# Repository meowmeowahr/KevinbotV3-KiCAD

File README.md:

# This repository has moved

Kevinbot Core and the Kevinbot P2 Board have split into separate repositories, and are now located in the [Kevinbot Robotics](https://github.com/Kevinbot-Robotics) organization.

## Kevinbot Core (aka RevB)

https://github.com/Kevinbot-Robotics/kevinbot_core

## Kevinbot P2 Board (aka RevA)

https://github.com/Kevinbot-Robotics/kevinbot_p2_board

## PCBWay

</img>

Thanks to PCBWay for providing high-quality PCB prototypes.

I would recommend them for any of your PCB needs. They offer fast turnaround and shipping.

[Get a Quote Here](https://www.pcbway.com/orderonline.aspx)

</img>
</img>

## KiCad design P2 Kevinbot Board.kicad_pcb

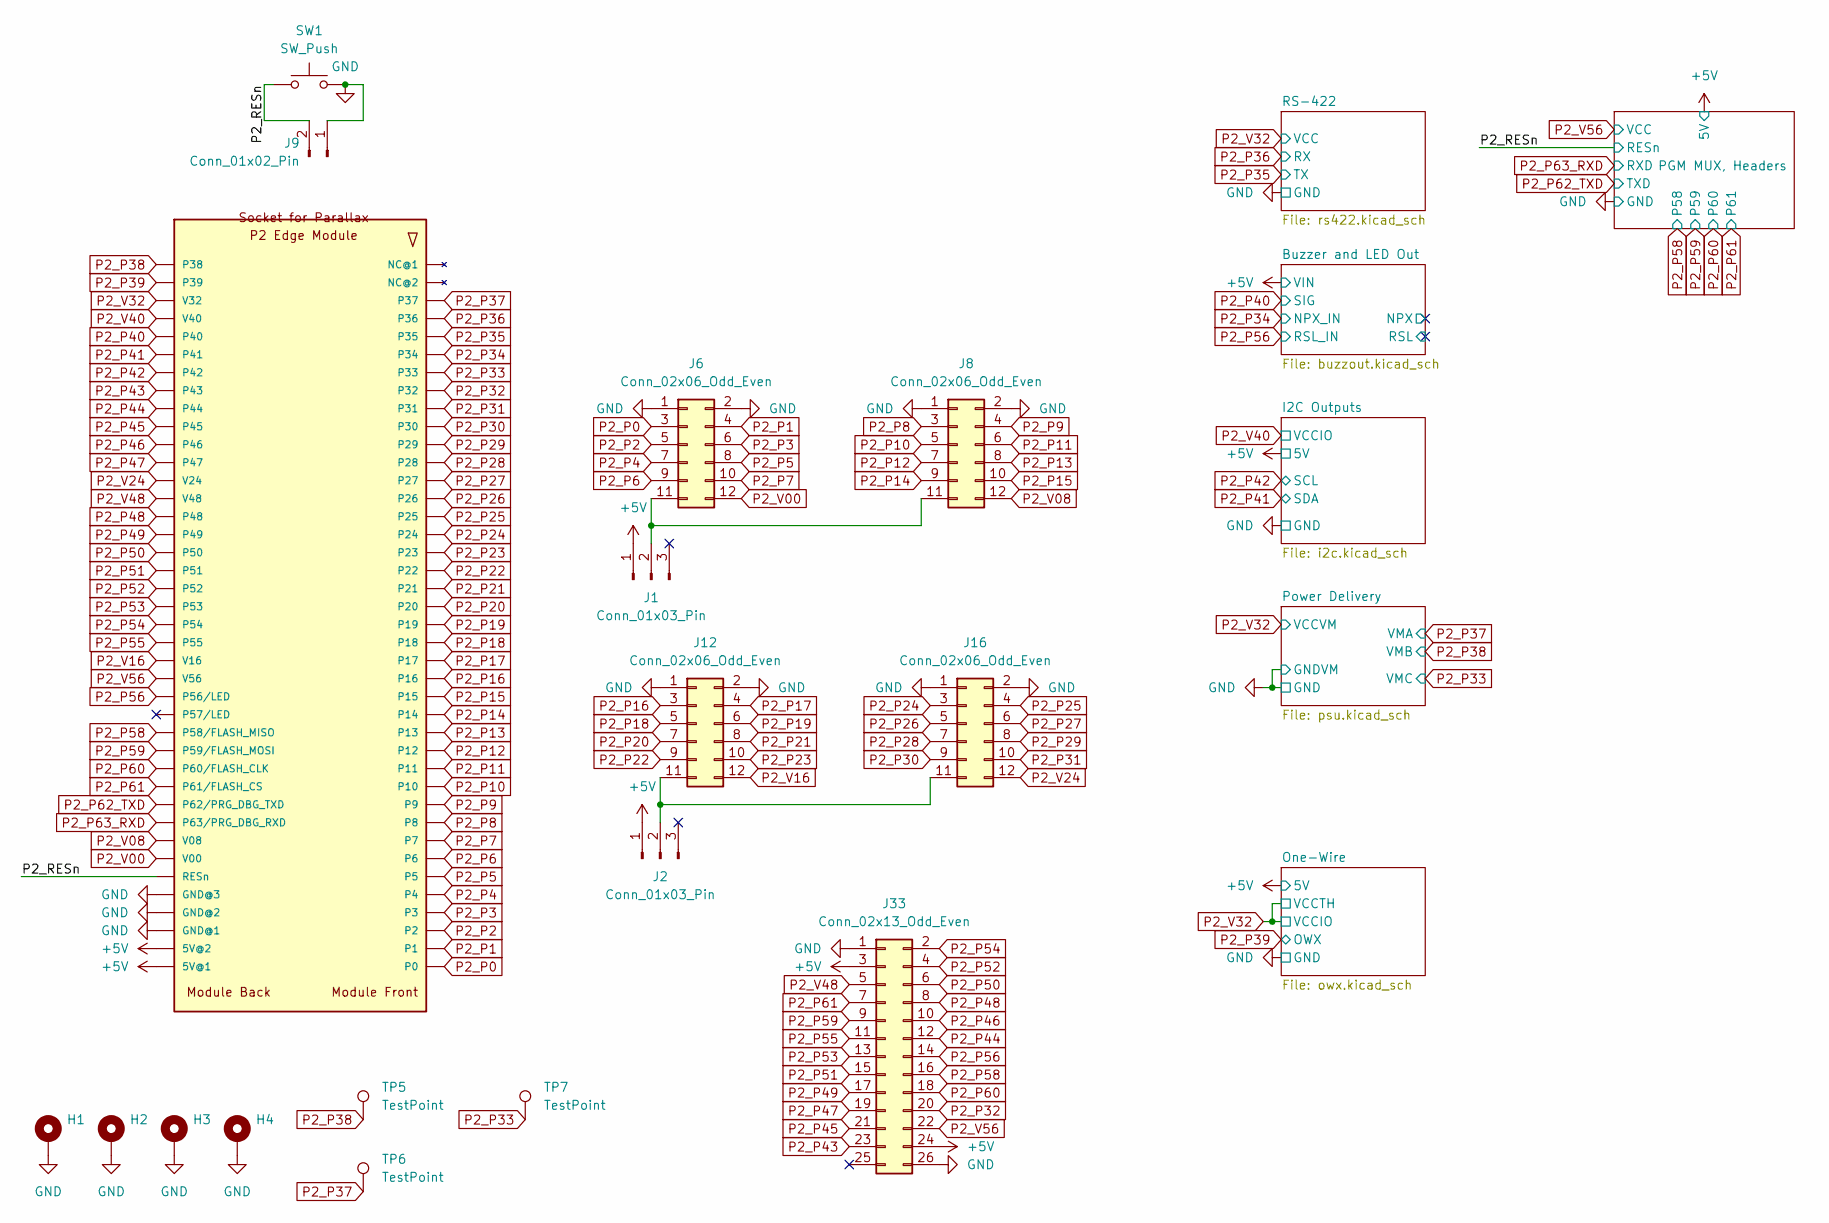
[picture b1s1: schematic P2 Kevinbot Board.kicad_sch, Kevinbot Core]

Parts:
H1, H2, H3, H4: MountingHole_Pad; MountingHole_3.2mm_M3_Pad
J1, J2: Conn_01x03_Pin; PinHeader_1x03_P2.00mm_Vertical; Part Number 2PH1-03-UA, SPN02SXCN-RC
J6, J8, J12, J16: Conn_02x06_Odd_Even; PinHeader_2x06_P2.54mm_Vertical; Part Number G800W590018EU
J9: Conn_01x02_Pin; Molex_Nano-Fit_105309-xx02_1x02_P2.50mm_Vertical; Part Number 1053091102
J33: Conn_02x13_Odd_Even; PinHeader_2x13_P1.27mm_Vertical; Part Number 3220-26-0100-00
SW1: SW_Push; SW_SPST_PTS645Sx43SMTR92; Part Number PTS645SM43SMTR92 LFS
TP5, TP6, TP7: TestPoint; TestPoint_Pad_D1.0mm
U1: P2_EDGE_MODULE_SOCKET; Card_Edge_TH_RA_1.27mm_80p; Part Number 450-00308

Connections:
+5V: J1.1, J2.1, J33.3, J33.24, U1.41 (5V@1), U1.42 (5V@2); also elsewhere on the board
/P2_RESn: J9.2, SW1.1, U1.46 (RESn); also elsewhere on the board
GND: H1.1, H2.1, H3.1, H4.1, J6.1, J6.2, J8.1, J8.2, J9.1, J12.1, J12.2, J16.1, J16.2, J33.1, J33.26, SW1.2, U1.43 (GND@1), U1.44 (GND@2), U1.45 (GND@3); also elsewhere on the board
unnamed: J1.2, J6.11, J8.11
unnamed: J2.2, J12.11, J16.11
P2_P0: J6.3, U1.40 (P0)
P2_P1: J6.4, U1.39 (P1)
P2_P2: J6.5, U1.38 (P2)
P2_P3: J6.6, U1.37 (P3)
P2_P4: J6.7, U1.36 (P4)
P2_P5: J6.8, U1.35 (P5)
P2_P6: J6.9, U1.34 (P6)
P2_P7: J6.10, U1.33 (P7)
P2_P8: J8.3, U1.32 (P8)
P2_P9: J8.4, U1.31 (P9)
P2_P10: J8.5, U1.30 (P10)
P2_P11: J8.6, U1.29 (P11)
P2_P12: J8.7, U1.28 (P12)
P2_P13: J8.8, U1.27 (P13)
P2_P14: J8.9, U1.26 (P14)
P2_P15: J8.10, U1.25 (P15)
P2_P16: J12.3, U1.24 (P16)
P2_P17: J12.4, U1.23 (P17)
P2_P18: J12.5, U1.22 (P18)
P2_P19: J12.6, U1.21 (P19)
P2_P20: J12.7, U1.20
P2_P21: J12.8, U1.19 (P21)
P2_P22: J12.9, U1.18 (P22)
P2_P23: J12.10, U1.17 (P23)
P2_P24: J16.3, U1.16 (P24)
P2_P25: J16.4, U1.15 (P25)
P2_P26: J16.5, U1.14 (P26)
P2_P27: J16.6, U1.13 (P27)
P2_P28: J16.7, U1.12 (P28)
P2_P29: J16.8, U1.11 (P29)
P2_P30: J16.9, U1.10 (P30)
P2_P31: J16.10, U1.9 (P31)
P2_P32: J33.20, U1.8 (P32)
P2_P33: TP7.1, U1.7 (P33); also elsewhere on the board
P2_P34: U1.6 (P34); also elsewhere on the board
P2_P35: U1.5 (P35); also elsewhere on the board
P2_P36: U1.4 (P36); also elsewhere on the board
P2_P37: TP6.1, U1.3 (P37); also elsewhere on the board
P2_P38: TP5.1, U1.80 (P38); also elsewhere on the board
P2_P39: U1.79 (P39); also elsewhere on the board
P2_P40: U1.76 (P40); also elsewhere on the board
P2_P41: U1.75 (P41); also elsewhere on the board
P2_P42: U1.74 (P42); also elsewhere on the board
P2_P43: J33.23, U1.73 (P43)
P2_P44: J33.12, U1.72 (P44)
P2_P45: J33.21, U1.71 (P45)
P2_P46: J33.10, U1.70 (P46)
P2_P47: J33.19, U1.69 (P47)
P2_P48: J33.8, U1.66 (P48)
P2_P49: J33.17, U1.65 (P49)
P2_P50: J33.6, U1.64 (P50)
P2_P51: J33.15, U1.63 (P51)
P2_P52: J33.4, U1.62 (P52)
P2_P53: J33.13, U1.61 (P53)
P2_P54: J33.2, U1.60 (P54)
P2_P55: J33.11, U1.59 (P55)
P2_P56: J33.14, U1.56 (P56/LED); also elsewhere on the board
P2_P58: J33.16, U1.54 (P58/FLASH_MISO); also elsewhere on the board
P2_P59: J33.9, U1.53 (P59/FLASH_MOSI); also elsewhere on the board
P2_P60: J33.18, U1.52 (P60/FLASH_CLK); also elsewhere on the board
P2_P61: J33.7, U1.51 (P61/FLASH_CS); also elsewhere on the board
P2_P62_TXD: U1.50 (P62/PRG_DBG_TXD); also elsewhere on the board
P2_P63_RXD: U1.49 (P63/PRG_DBG_RXD); also elsewhere on the board
P2_V00: J6.12, U1.47 (V00)
P2_V08: J8.12, U1.48 (V08)
P2_V16: J12.12, U1.58 (V16)
P2_V24: J16.12, U1.68 (V24)
P2_V32: U1.78 (V32); also elsewhere on the board
P2_V40: U1.77 (V40); also elsewhere on the board
P2_V48: J33.5, U1.67 (V48)
P2_V56: J33.22, U1.57 (V56); also elsewhere on the board

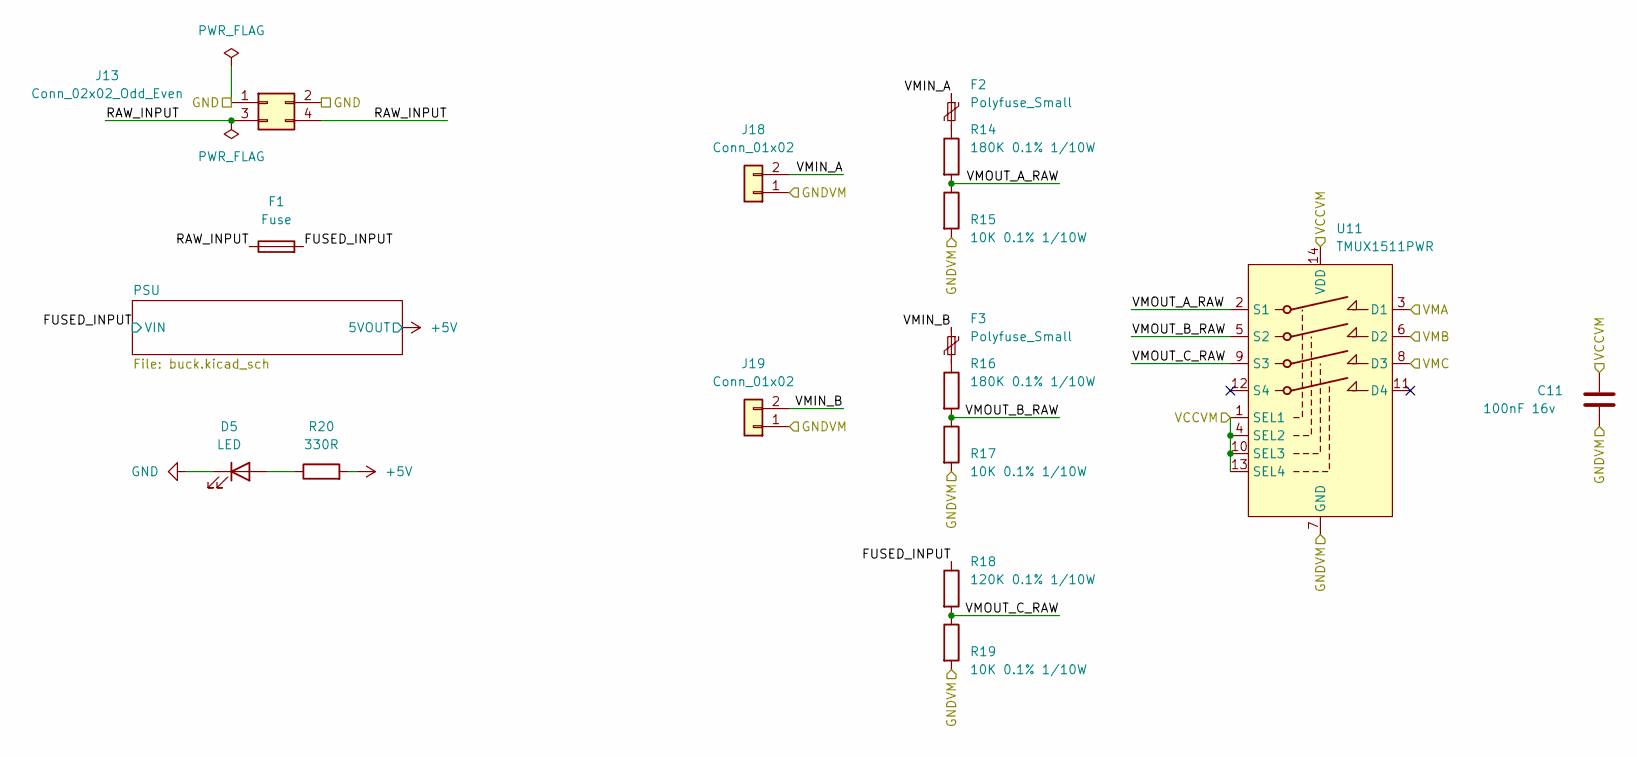
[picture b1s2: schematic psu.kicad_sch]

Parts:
C11: 100nF 16v; C_0402_1005Metric; Part Number GRM155R71C104KA88D
D5: LED; LED_0603_1608Metric; Part Number 150080SS75000
F1: Fuse; Fuseholder_Blade_Mini_Keystone_3568; Part Number 3568
F2, F3: Polyfuse_Small; Fuse_1206_3216Metric_Pad1.42x1.75mm_HandSolder; Part Number 0ZCJ0005FF2E
J13: Conn_02x02_Odd_Even; Molex_Micro-Fit_3.0_43045-0400_2x02_P3.00mm_Horizontal; Part Number 0430450400
J18, J19: Conn_01x02; Molex_Nano-Fit_105313-xx02_1x02_P2.50mm_Horizontal; Part Number 1053132102
R14, R16: 180K 0.1% 1/10W; R_0603_1608Metric; Part Number RT0603BRD07180KL
R15, R17, R19: 10K 0.1% 1/10W; R_0603_1608Metric; Part Number RT0603BRD0710KL
R18: 120K 0.1% 1/10W; R_0603_1608Metric; Part Number RT0603BRD07120KL
R20: 330R; R_0603_1608Metric; Part Number RC0402FR-07330RL
U11: TMUX1511PWR; TSSOP-14_4.4x5mm_P0.65mm; Part Number TMUX1511PWR

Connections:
+5V: R20.2; also elsewhere on the board
/Power Delivery/FUSED_INPUT: F1.2, R18.1; also elsewhere on the board
/Power Delivery/RAW_INPUT: F1.1, J13.3, J13.4
/Power Delivery/VMIN_A: F2.1, J18.2
/Power Delivery/VMIN_B: F3.1, J19.2
/Power Delivery/VMOUT_A_RAW: R14.2, R15.1, U11.2 (S1)
/Power Delivery/VMOUT_B_RAW: R16.2, R17.1, U11.5 (S2)
/Power Delivery/VMOUT_C_RAW: R18.2, R19.1, U11.9 (S3)
GND: C11.1, D5.1 (K), J13.1, J13.2, J18.1, J19.1, R15.2, R17.2, R19.2, U11.7 (GND); also elsewhere on the board
unnamed: D5.2 (A), R20.1
unnamed: F2.2, R14.1
unnamed: F3.2, R16.1
P2_P33: U11.8 (D3); also elsewhere on the board
P2_P37: U11.3 (D1); also elsewhere on the board
P2_P38: U11.6 (D2); also elsewhere on the board
P2_V32: C11.2, U11.1 (SEL1), U11.4 (SEL2), U11.10 (SEL3), U11.13 (SEL4), U11.14 (VDD); also elsewhere on the board

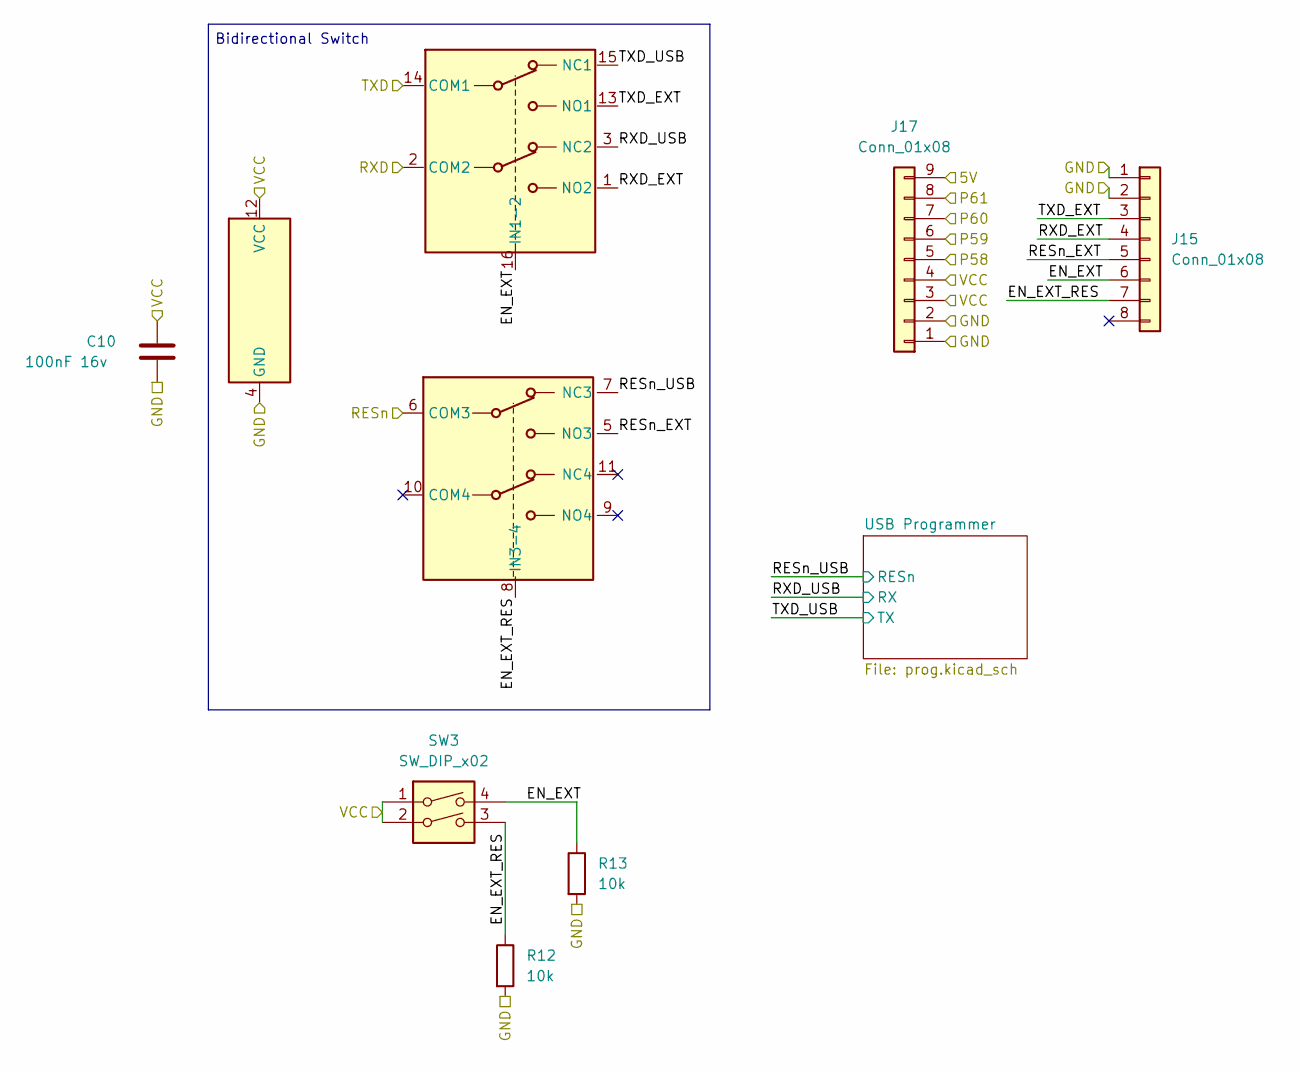
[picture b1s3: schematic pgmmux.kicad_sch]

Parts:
C10: 100nF 16v; C_0402_1005Metric; Part Number GRM155R71C104KA88D
J15: Conn_01x08; PinSocket_1x08_P2.54mm_Vertical; Part Number PPTC081LFBN-RC
J17: Conn_01x08; PinSocket_1x09_P2.54mm_Vertical; Part Number PPTC091LFBN-RC
R12, R13: 10k; R_0402_1005Metric; Part Number RC0402FR-0710KL
SW3: SW_DIP_x02; SW_DIP_SPSTx02_Slide_Copal_CHS-02A_W5.08mm_P1.27mm_JPin; Part Number CHS-02TA
U10: TS3A44159PWR; TSSOP-16_4.4x5mm_P0.65mm; Part Number TS3A44159PWR

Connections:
+5V: J17.9; also elsewhere on the board
/P2_RESn: U10.6 (COM3); also elsewhere on the board
/PGM MUX, Headers/EN_EXT: J15.6, R13.1, SW3.4, U10.16 (IN1-2)
/PGM MUX, Headers/EN_EXT_RES: J15.7, R12.1, SW3.3, U10.8 (IN3-4)
/PGM MUX, Headers/RESn_EXT: J15.5, U10.5 (NO3)
/PGM MUX, Headers/RESn_USB: U10.7 (NC3); also elsewhere on the board
/PGM MUX, Headers/RXD_EXT: J15.4, U10.1 (NO2)
/PGM MUX, Headers/RXD_USB: U10.3 (NC2); also elsewhere on the board
/PGM MUX, Headers/TXD_EXT: J15.3, U10.13 (NO1)
/PGM MUX, Headers/TXD_USB: U10.15 (NC1); also elsewhere on the board
GND: C10.1, J15.1, J15.2, J17.1, J17.2, R12.2, R13.2, U10.4 (GND); also elsewhere on the board
P2_P58: J17.5; also elsewhere on the board
P2_P59: J17.6; also elsewhere on the board
P2_P60: J17.7; also elsewhere on the board
P2_P61: J17.8; also elsewhere on the board
P2_P62_TXD: U10.14 (COM1); also elsewhere on the board
P2_P63_RXD: U10.2 (COM2); also elsewhere on the board
P2_V56: C10.2, J17.3, J17.4, SW3.1, SW3.2, U10.12 (VCC); also elsewhere on the board

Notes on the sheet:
Bidirectional Switch

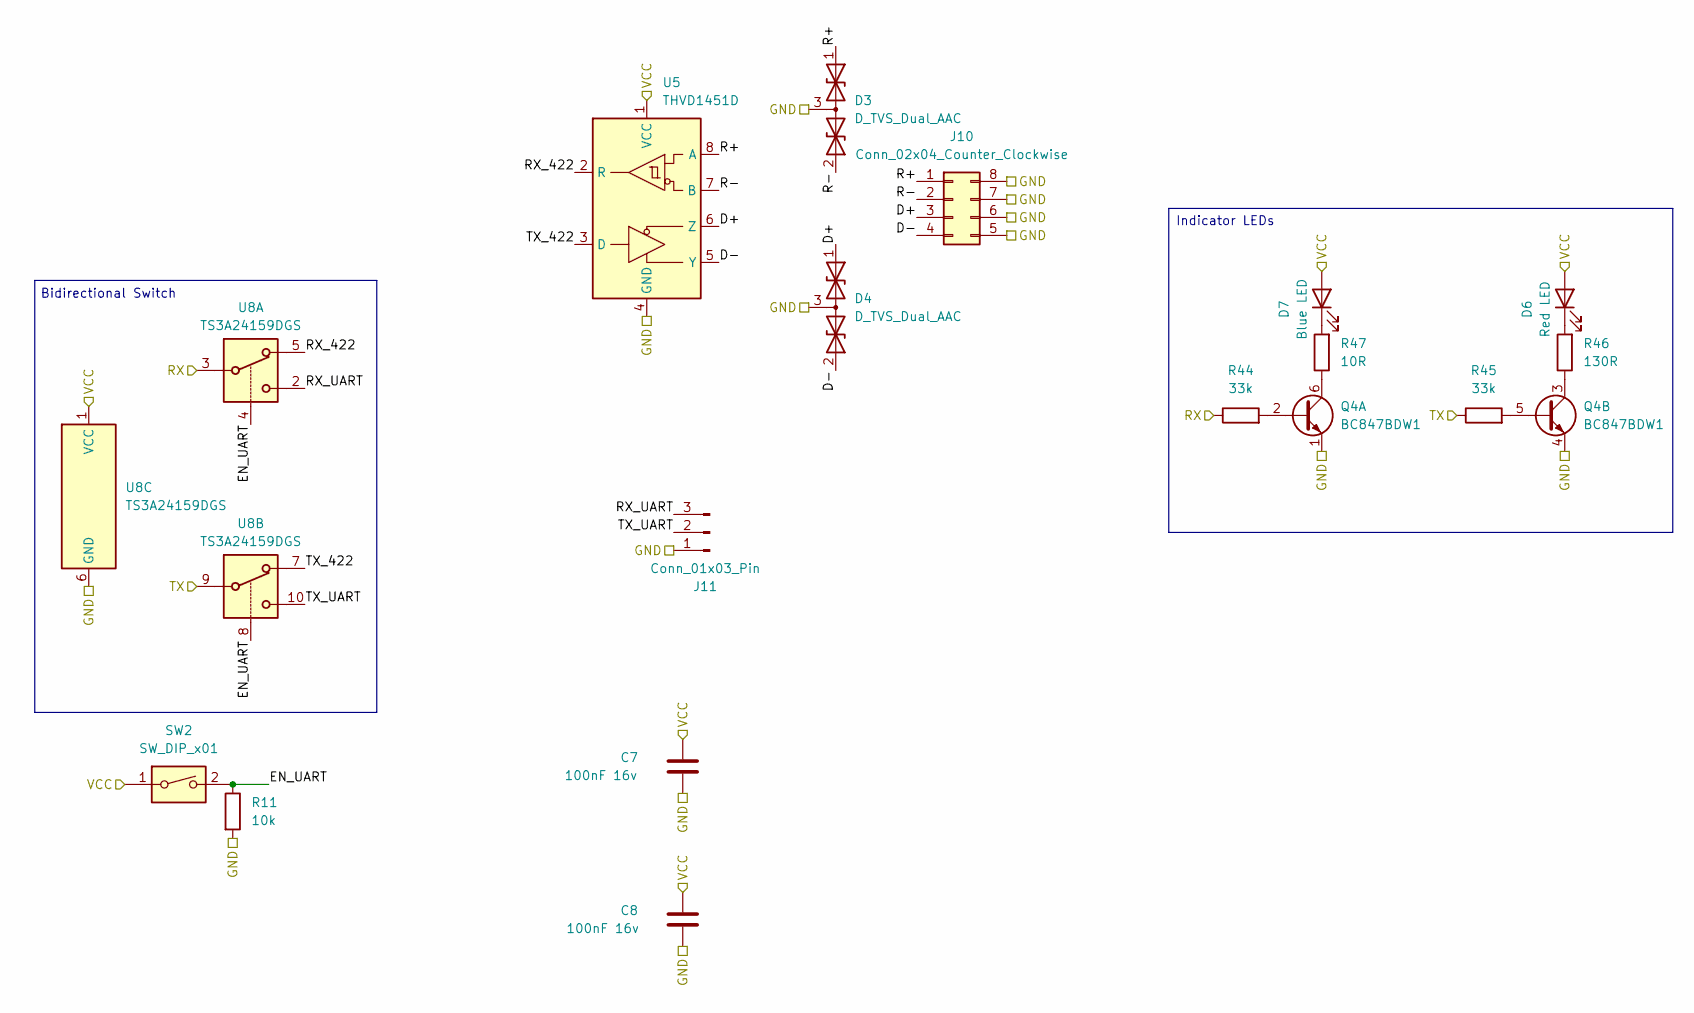
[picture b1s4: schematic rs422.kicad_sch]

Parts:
C7, C8: 100nF 16v; C_0402_1005Metric; Part Number GRM155R71C104KA88D
D3, D4: D_TVS_Dual_AAC; SOT-23; Part Number D5V0L2B3SO-7
D6: Red LED; LED_0603_1608Metric; Part Number 150060RS75000
D7: Blue LED; LED_0603_1608Metric; Part Number 150060BS75000
J10: Conn_02x04_Counter_Clockwise; Molex_Nano-Fit_105310-xx08_2x04_P2.50mm_Vertical; Part Number 1053101108
J11: Conn_01x03_Pin; JST_PH_B3B-PH-K_1x03_P2.00mm_Vertical; Part Number B3B-PH-K-S
Q4: BC847BDW1; SOT-363_SC-70-6; Part Number BC847BDW1T1G
R11: 10k; R_0402_1005Metric; Part Number RC0402FR-0710KL
R44, R45: 33k; R_0402_1005Metric; Part Number RC0402FR-0733KL
R46: 130R; R_0402_1005Metric; Part Number RC0402FR-07130RL
R47: 10R; R_0402_1005Metric; Part Number RC0402FR-0710RL
SW2: SW_DIP_x01; SW_DIP_SPSTx01_Slide_Copal_CHS-01A_W5.08mm_P1.27mm_JPin; Part Number CHS-01A
U5: THVD1451D; SOIC-8_3.9x4.9mm_P1.27mm; Part Number THVD1451D
U8: TS3A24159DGS; TSSOP-10_3x3mm_P0.5mm; Part Number TS3A24159DGSR

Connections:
/RS-422/D+: D4.1 (A1), J10.3, U5.6 (Z)
/RS-422/D-: D4.2 (A2), J10.4, U5.5 (Y)
/RS-422/EN_UART: R11.1, SW2.2, U8.4, U8.8
/RS-422/R+: D3.1 (A1), J10.1, U5.8 (A)
/RS-422/R-: D3.2 (A2), J10.2, U5.7 (B)
/RS-422/RX_422: U5.2 (R), U8.5
/RS-422/RX_UART: J11.3, U8.2
/RS-422/TX_422: U5.3 (D), U8.7
/RS-422/TX_UART: J11.2, U8.10
GND: C7.1, C8.1, D3.3 (common), D4.3 (common), J10.5, J10.6, J10.7, J10.8, J11.1, Q4.1 (E1), Q4.4 (E2), R11.2, U5.4 (GND), U8.6 (GND); also elsewhere on the board
unnamed: D6.1 (K), R46.2
unnamed: D7.1 (K), R47.2
unnamed: Q4.2 (B1), R44.2
unnamed: Q4.6 (C1), R47.1
unnamed: Q4.5 (B2), R45.2
unnamed: Q4.3 (C2), R46.1
P2_P35: R45.1, U8.9; also elsewhere on the board
P2_P36: R44.1, U8.3; also elsewhere on the board
P2_V32: C7.2, C8.2, D6.2 (A), D7.2 (A), SW2.1, U5.1 (VCC), U8.1 (VCC); also elsewhere on the board

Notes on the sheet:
Bidirectional Switch
Indicator LEDs

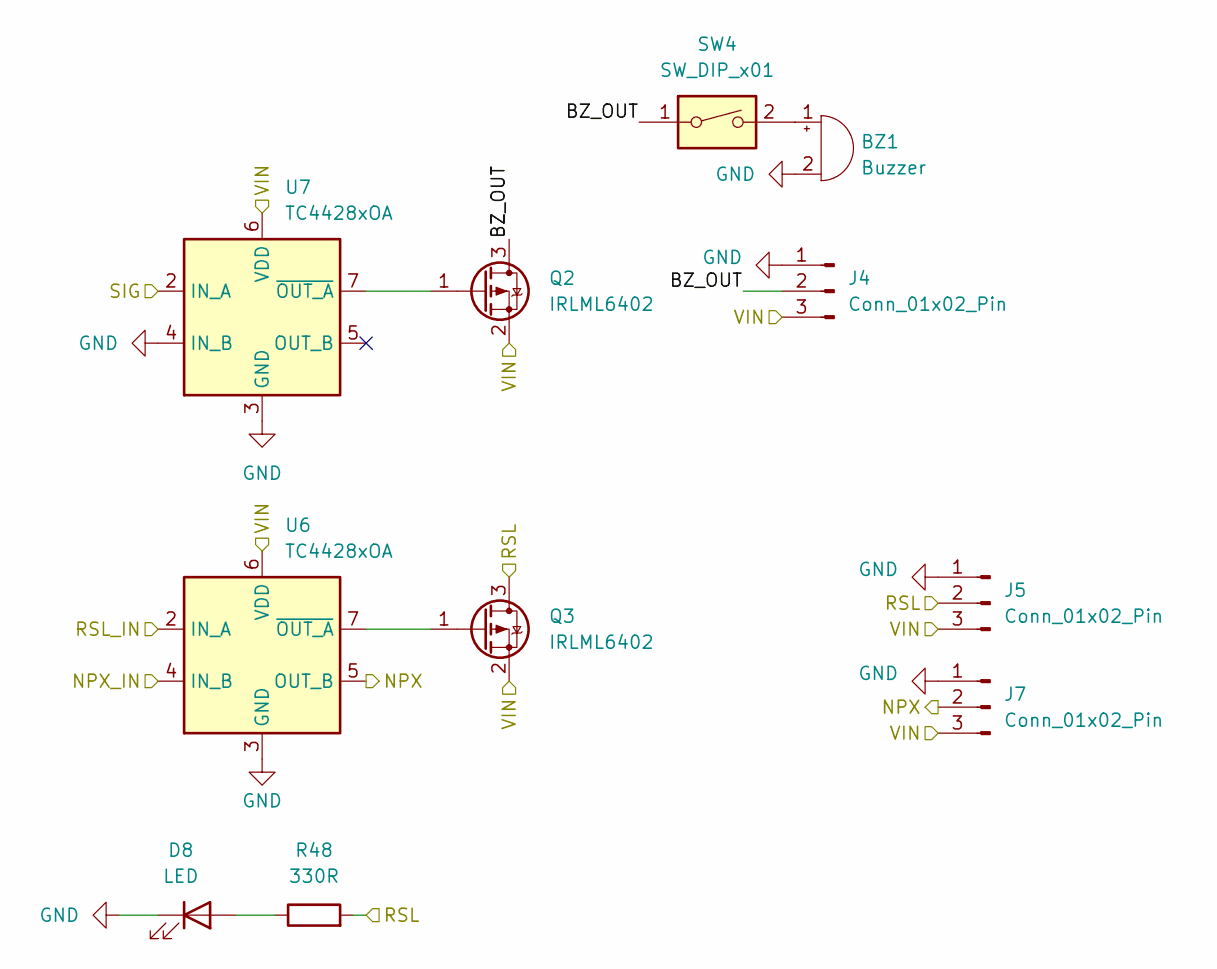
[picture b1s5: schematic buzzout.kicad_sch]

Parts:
BZ1: Buzzer; Buzzer_TDK_PS1240P02BT_D12.2mm_H6.5mm; Part Number PS1240P02BT
D8: LED; LED_0603_1608Metric; Part Number 150060YS75000
J4, J5, J7: Conn_01x02_Pin; Molex_Nano-Fit_105309-xx03_1x03_P2.50mm_Vertical; Part Number 1053091103
Q2, Q3: IRLML6402; SOT-23; Part Number IRLML6402TRPBF
R48: 330R; R_0603_1608Metric; Part Number RC0402FR-07330RL
SW4: SW_DIP_x01; SW_DIP_SPSTx01_Slide_Copal_CHS-01A_W5.08mm_P1.27mm_JPin; Part Number CHS-01A
U6, U7: TC4428xOA; SOIC-8_3.9x4.9mm_P1.27mm; Part Number TC4428EOA713

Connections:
+5V: J4.3, J5.3, J7.3, Q2.2 (S), Q3.2 (S), U6.6 (VDD), U7.6 (VDD); also elsewhere on the board
/Buzzer and LED Out/BZ_OUT: J4.2, Q2.3 (D), SW4.1
/Buzzer and LED Out/NPX: J7.2, U6.5 (OUT_B)
/Buzzer and LED Out/RSL: J5.2, Q3.3 (D), R48.2
GND: BZ1.2 (-), D8.1 (K), J4.1, J5.1, J7.1, U6.3 (GND), U7.3 (GND), U7.4 (IN_B); also elsewhere on the board
unnamed: BZ1.1 (+), SW4.2
unnamed: D8.2 (A), R48.1
unnamed: Q2.1 (G), U7.7 (~OUT_A)
unnamed: Q3.1 (G), U6.7 (~OUT_A)
P2_P34: U6.4 (IN_B); also elsewhere on the board
P2_P40: U7.2 (IN_A); also elsewhere on the board
P2_P56: U6.2 (IN_A); also elsewhere on the board

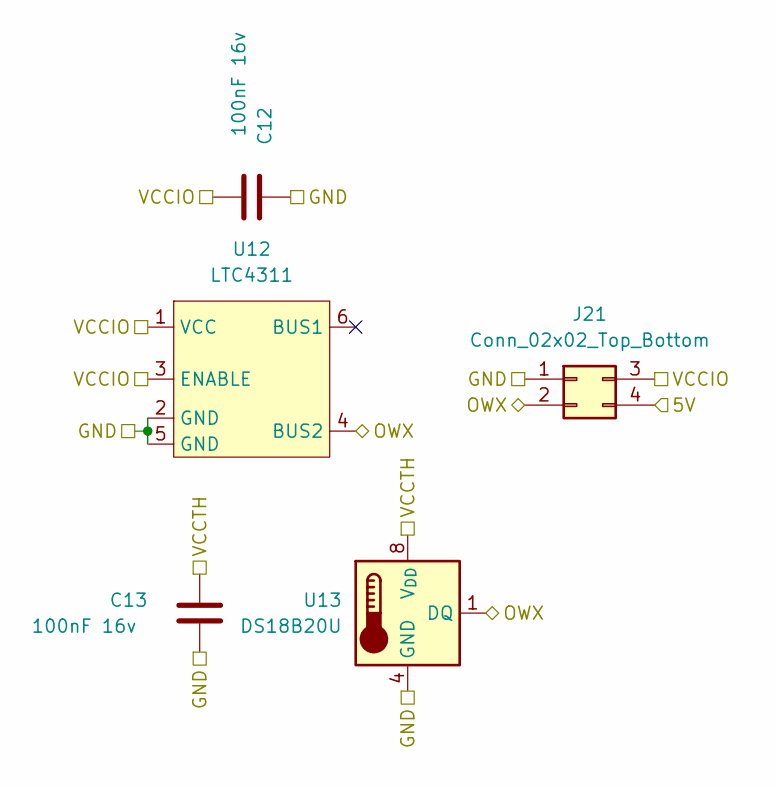
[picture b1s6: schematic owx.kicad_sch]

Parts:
C12, C13: 100nF 16v; C_0402_1005Metric; Part Number GRM155R71C104KA88D
J21: Conn_02x02_Top_Bottom; Molex_Nano-Fit_105310-xx04_2x02_P2.50mm_Vertical; Part Number 1053101104
U12: LTC4311; SOT-363_SC-70-6; Part Number LTC4311CSC6#TRPBF
U13: DS18B20U; MSOP-8_3x3mm_P0.65mm; Part Number DS18B20U+T&R

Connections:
+5V: J21.4; also elsewhere on the board
GND: C12.2, C13.1, J21.1, U12.2 (GND), U12.5 (GND), U13.4 (GND); also elsewhere on the board
P2_P39: J21.2, U12.4 (BUS2), U13.1 (DQ); also elsewhere on the board
P2_V32: C12.1, C13.2, J21.3, U12.1 (VCC), U12.3 (ENABLE), U13.8 (V_{DD}); also elsewhere on the board

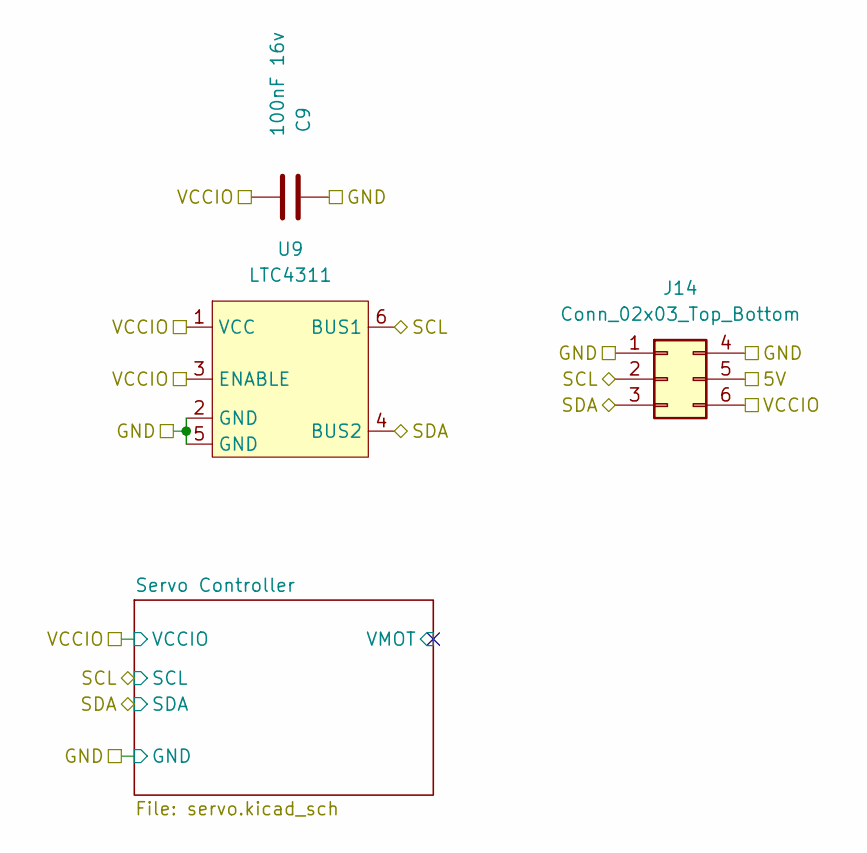
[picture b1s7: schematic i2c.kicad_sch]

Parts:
C9: 100nF 16v; C_0402_1005Metric; Part Number GRM155R71C104KA88D
J14: Conn_02x03_Top_Bottom; Molex_Nano-Fit_105310-xx06_2x03_P2.50mm_Vertical; Part Number 1053101106
U9: LTC4311; SOT-363_SC-70-6; Part Number LTC4311CSC6#TRPBF

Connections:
+5V: J14.5; also elsewhere on the board
GND: C9.2, J14.1, J14.4, U9.2 (GND), U9.5 (GND); also elsewhere on the board
P2_P41: J14.3, U9.4 (BUS2); also elsewhere on the board
P2_P42: J14.2, U9.6 (BUS1); also elsewhere on the board
P2_V40: C9.1, J14.6, U9.1 (VCC), U9.3 (ENABLE); also elsewhere on the board

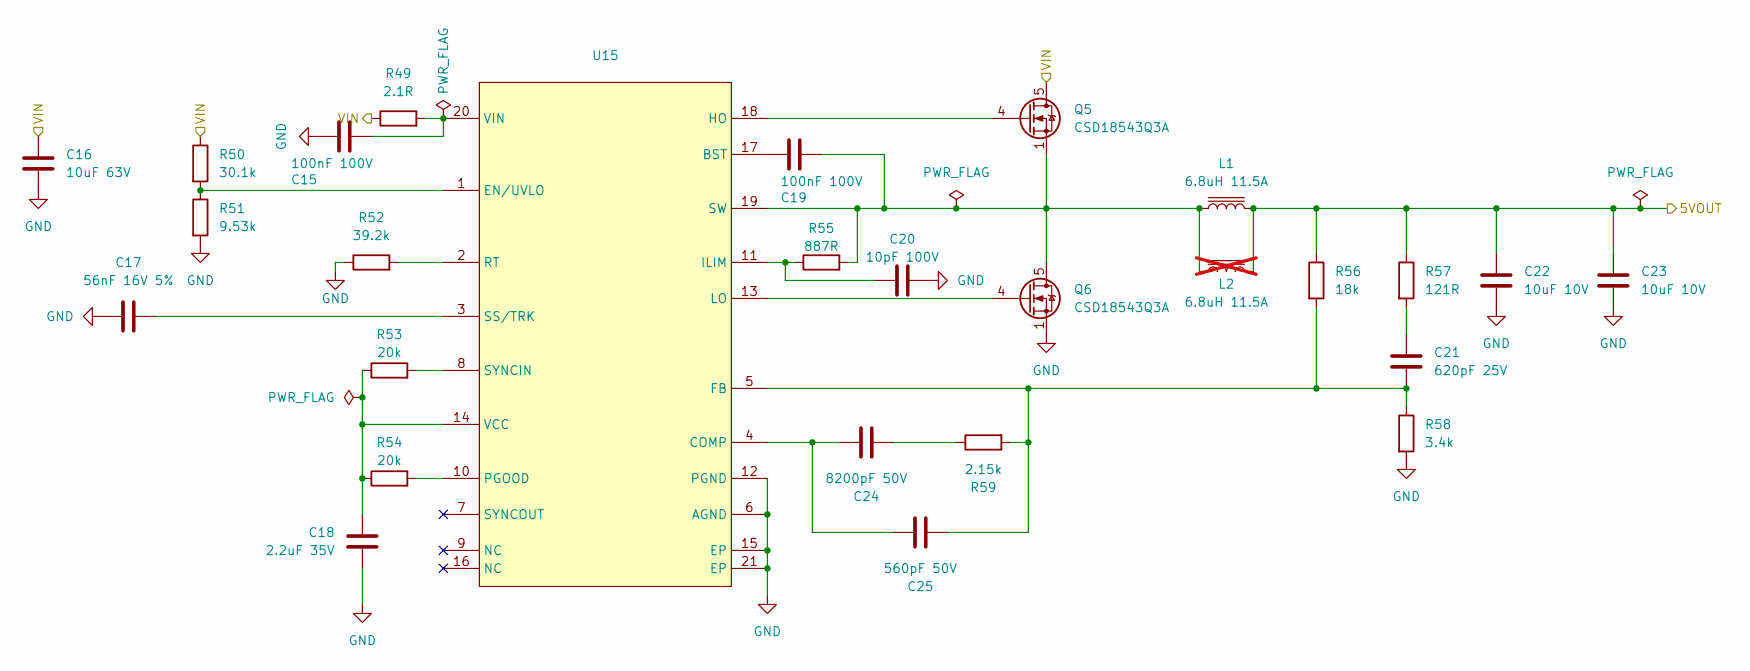
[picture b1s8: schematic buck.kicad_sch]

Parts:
C15, C19: 100nF 100V; C_0603_1608Metric; Part Number C1608X7S2A104K080AB
C16: 10uF 63V; C_1210_3225Metric; Part Number CL32B106KMVNNWE
C17: 56nF 16V 5%; C_0603_1608Metric; Part Number C0603C563J4RACTU
C18: 2.2uF 35V; C_0603_1608Metric; Part Number C1608X5R1V225K080AC
C20: 10pF 100V; C_0603_1608Metric; Part Number GCM1885C2A100JA16D
C21: 620pF 25V; C_0603_1608Metric; Part Number C0603C621J3GACTU
C22, C23: 10uF 10V; C_1210_3225Metric; Part Number C1210C106K8PACTU
C24: 8200pF 50V; C_0603_1608Metric; Part Number GCM1885C1H822JA16D
C25: 560pF 50V; C_0603_1608Metric; Part Number C0603C561J5GACTU
L1: 6.8uH 11.5A; L_Bourns_SRP1245A; Part Number SRP1265A-6R8M
L2: 6.8uH 11.5A; L_Coilcraft_XAL7070-XXX-NOSILK; Part Number XAL7070-682MEC; not fitted
Q5, Q6: CSD18543Q3A; VSON-8_3.3x3.3mm_P0.65mm_NexFET; Part Number CSD18543Q3A
R49: 2.1R; R_0603_1608Metric; Part Number CRCW06032R10FKEA
R50: 30.1k; R_0603_1608Metric; Part Number RC0603FR-0730K1L
R51: 9.53k; R_0603_1608Metric; Part Number RC0603FR-079K53L
R52: 39.2k; R_0603_1608Metric; Part Number RC0603FR-0739K2L
R53, R54: 20k; R_0603_1608Metric; Part Number CRCW060320K0FKEA
R55: 887R; R_0603_1608Metric; Part Number RC0603FR-07887RL
R56: 18k; R_0603_1608Metric; Part Number RC0603FR-0718KL
R57: 121R; R_0603_1608Metric; Part Number RC0603FR-07121RL
R58: 3.4k; R_0603_1608Metric; Part Number RC0603FR-073K4L
R59: 2.15k; R_0603_1608Metric; Part Number RC0603FR-072K15L
U15: Texas_RGY_R-PVQFN-N20_EP2.05x3.05mm_ThermalVias; Part Number LM25145RGYR

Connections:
+5V: C22.1, C23.1, L1.2, L2.2, R56.1, R57.1; also elsewhere on the board
/Power Delivery/FUSED_INPUT: C16.1, Q5.5 (D), R49.1, R50.1; also elsewhere on the board
GND: C15.2, C16.2, C17.2, C18.2, C20.2, C22.2, C23.2, Q6.1 (S), Q6.2 (S), Q6.3 (S), R51.2, R52.1, R58.2, U15.6 (AGND), U15.12 (PGND), U15.15 (EP), U15.21 (EP); also elsewhere on the board
unnamed: C21.1, R57.2
unnamed: C24.2, R59.1
unnamed: Q5.4 (G), U15.18 (HO)
unnamed: C19.1, L1.1, L2.1, Q5.1 (S), Q5.2 (S), Q5.3 (S), Q6.5 (D), R55.2, U15.19 (SW)
unnamed: Q6.4 (G), U15.13 (LO)
unnamed: C19.2, U15.17 (BST)
unnamed: C24.1, C25.1, U15.4 (COMP)
unnamed: R50.2, R51.1, U15.1 (EN/UVLO)
unnamed: C21.2, C25.2, R56.2, R58.1, R59.2, U15.5 (FB)
unnamed: C20.1, R55.1, U15.11 (ILIM)
unnamed: R54.2, U15.10 (PGOOD)
unnamed: R52.2, U15.2 (RT)
unnamed: C17.1, U15.3 (SS/TRK)
unnamed: R53.2, U15.8 (SYNCIN)
unnamed: C18.1, R53.1, R54.1, U15.14 (VCC)
unnamed: C15.1, R49.2, U15.20 (VIN)

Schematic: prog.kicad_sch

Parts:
C1, C5: 10nF 16v; C_0402_1005Metric; Part Number GRM155R71C103KA01D
C2, C3: 4.7uF 10v; C_0402_1005Metric; Part Number GRM155R61A475MEAAD
C4, C6: 100nF 16v; C_0402_1005Metric; Part Number GRM155R71C104KA88D
D1: Red LED; LED_0603_1608Metric; Part Number 150060RS75000
D2: Blue LED; LED_0603_1608Metric; Part Number 150060BS75000
FB1: 220R; L_0603_1608Metric; Part Number MPZ1608S221ATA00
J3: USB_C_Receptacle_USB2.0_16P; USB_C_Receptacle_GCT_USB4105-xx-A_16P_TopMnt_Horizontal; Part Number USB4105-GF-A
Q1: MUN5211T1G; SOT-323_SC-70; Part Number MUN5211T1G
R1, R2: 5.1k; R_0402_1005Metric; Part Number RC0402FR-075K1L
R3, R4: 27R; R_0402_1005Metric; Part Number RC0402FR-0727RL
R5, R6: 240R; R_0402_1005Metric; Part Number RC0402FR-07240RL
R7: 470k; R_0402_1005Metric; Part Number RC0402FR-07470KL
R8, R9, R10: 100k; R_0402_1005Metric; Part Number RC0402FR-07100KL
TP1, TP2, TP3, TP4: TestPoint; TestPoint_Pad_D1.0mm
U2: FT231XS; SSOP-20_3.9x8.7mm_P0.635mm; Part Number FT231XS-R
U3, U4: 74LVC1G126; SOT-353_SC-70-5; Part Number 74LVC1G126SE-7

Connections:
+5VUSB: C2.1, C3.1, FB1.2, R5.2, U2.15 (VCC)
/PGM MUX, Headers/RESn_USB: Q1.3 (C); also elsewhere on the board
/PGM MUX, Headers/RXD_USB: R6.1, R7.1; also elsewhere on the board
/PGM MUX, Headers/TXD_USB: R10.1, U4.4; also elsewhere on the board
/PGM MUX, Headers/USB Programmer/DTR: C5.1, U2.1 (~DTR)
/PGM MUX, Headers/USB Programmer/FT_RX: U2.4 (RXD), U3.4
/PGM MUX, Headers/USB Programmer/FT_TX: U2.20 (TXD), U4.2
/PGM MUX, Headers/USB Programmer/SLEEP: R8.2, TP1.1, U2.17 (CBUS1), U3.1
/PGM MUX, Headers/USB Programmer/TXDEN: R9.2, TP2.1, U2.10 (CBUS2), U4.1
/PGM MUX, Headers/USB Programmer/VCCIO: C4.2, C6.2, R10.2, U2.3 (VCCIO), U2.13 (3V3OUT), U2.14 (~RESET), U3.5 (VCC), U4.5 (VCC)
GND: C1.2, C2.2, C3.2, C4.1, C6.1, J3.A1 (GND), J3.A12 (GND), J3.B1 (GND), J3.B12 (GND), J3.S1 (SHIELD), Q1.2 (E), R1.1, R2.1, R7.2, R8.1, R9.1, U2.6 (GND), U2.16 (GND), U3.3 (GND), U4.3 (GND); also elsewhere on the board
unnamed: D1.2 (A), D2.2 (A), R5.1
unnamed: D1.1 (K), TP3.1, U2.18 (CBUS0)
unnamed: D2.1 (K), TP4.1, U2.19 (CBUS3)
unnamed: J3.A5 (CC1), R2.2
unnamed: J3.B5 (CC2), R1.2
unnamed: J3.A6 (D+), J3.B6 (D+), R4.1
unnamed: J3.A7 (D-), J3.B7 (D-), R3.1
unnamed: C5.2, Q1.1 (B)
unnamed: R6.2, U3.2
unnamed: R3.2, U2.12 (USBDM)
unnamed: R4.2, U2.11 (USBDP)
VBUS: C1.1, FB1.1, J3.A4 (VBUS), J3.A9 (VBUS), J3.B4 (VBUS), J3.B9 (VBUS)

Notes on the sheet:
RX tri-state
TX tri-state
~20uS reset pulse
idle high

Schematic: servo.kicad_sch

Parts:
C14: 100nF 16v; C_0402_1005Metric; Part Number GRM155R71C104KA88D
C26: 1500uf; CP_Radial_D8.0mm_P3.50mm; Part Number A750KS158M0JAAE014
F4: Fuse; Fuseholder_Blade_Mini_Keystone_3568; Part Number 3568
J20, J22, J23, J24: Conn_04x03_Servo; ServoHeader_03x04_P2.54_Vertical
J25: Conn_02x02_Odd_Even; Molex_Micro-Fit_3.0_43045-0400_2x02_P3.00mm_Horizontal; Part Number 0430450400
R21, R22, R23, R24, R25, R26, R27: 10k; R_0402_1005Metric; Part Number RC0402FR-0710KL
R28, R29, R30, R31, R32, R33, R34, R35, R36, R37, R38, R39, R40, R41, R42, R43: 220R; R_0402_1005Metric; Part Number RC0402FR-07220RL
U14: PCA9685BS; QFN-28-1EP_6x6mm_P0.65mm_EP4.25x4.25mm; Part Number PCA9685BS,118

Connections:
/I2C Outputs/Servo Controller/S0: R40.1, U14.3 (LED0)
/I2C Outputs/Servo Controller/S1: R32.1, U14.4 (LED1)
/I2C Outputs/Servo Controller/S2: R41.1, U14.5 (LED2)
/I2C Outputs/Servo Controller/S3: R33.1, U14.6 (LED3)
/I2C Outputs/Servo Controller/S4: R42.1, U14.7 (LED4)
/I2C Outputs/Servo Controller/S5: R34.1, U14.8 (LED5)
/I2C Outputs/Servo Controller/S6: R43.1, U14.9 (LED6)
/I2C Outputs/Servo Controller/S7: R35.1, U14.10 (LED7)
/I2C Outputs/Servo Controller/S8: R36.1, U14.12 (LED8)
/I2C Outputs/Servo Controller/S9: R28.1, U14.13 (LED9)
/I2C Outputs/Servo Controller/S10: R37.1, U14.14 (LED10)
/I2C Outputs/Servo Controller/S11: R29.1, U14.15 (LED11)
/I2C Outputs/Servo Controller/S12: R38.1, U14.16 (LED12)
/I2C Outputs/Servo Controller/S13: R30.1, U14.17 (LED13)
/I2C Outputs/Servo Controller/S14: R39.1, U14.18 (LED14)
/I2C Outputs/Servo Controller/S15: R31.1, U14.19 (LED15)
/I2C Outputs/Servo Controller/VMOT: C26.1, F4.1, J20.2 (VIN), J22.2 (VIN), J23.2 (VIN), J24.2 (VIN)
GND: C14.1, C26.2, J20.1 (GND), J22.1 (GND), J23.1 (GND), J24.1 (GND), J25.1, J25.2, R21.1, R22.1, R23.1, R24.1, R25.1, R26.1, R27.1, U14.11 (VSS), U14.22 (EXTCLK), U14.29 (VSS); also elsewhere on the board
unnamed: J20.3 (S1), R28.2
unnamed: J20.4 (S2), R29.2
unnamed: J20.5 (S3), R30.2
unnamed: J20.6 (S4), R31.2
unnamed: J22.3 (S1), R32.2
unnamed: J22.4 (S2), R33.2
unnamed: J22.5 (S3), R34.2
unnamed: J22.6 (S4), R35.2
unnamed: J23.3 (S1), R36.2
unnamed: J23.4 (S2), R37.2
unnamed: J23.5 (S3), R38.2
unnamed: J23.6 (S4), R39.2
unnamed: J24.3 (S1), R40.2
unnamed: J24.4 (S2), R41.2
unnamed: J24.5 (S3), R42.2
unnamed: J24.6 (S4), R43.2
unnamed: F4.2, J25.3, J25.4
unnamed: R22.2, U14.26 (A0)
unnamed: R23.2, U14.27 (A1)
unnamed: R24.2, U14.28 (A2)
unnamed: R25.2, U14.1 (A3)
unnamed: R26.2, U14.2 (A4)
unnamed: R27.2, U14.21 (A5)
unnamed: R21.2, U14.20 (~OE)
P2_P41: U14.24 (SDA); also elsewhere on the board
P2_P42: U14.23 (SCL); also elsewhere on the board
P2_V40: C14.2, U14.25 (VDD); also elsewhere on the board
